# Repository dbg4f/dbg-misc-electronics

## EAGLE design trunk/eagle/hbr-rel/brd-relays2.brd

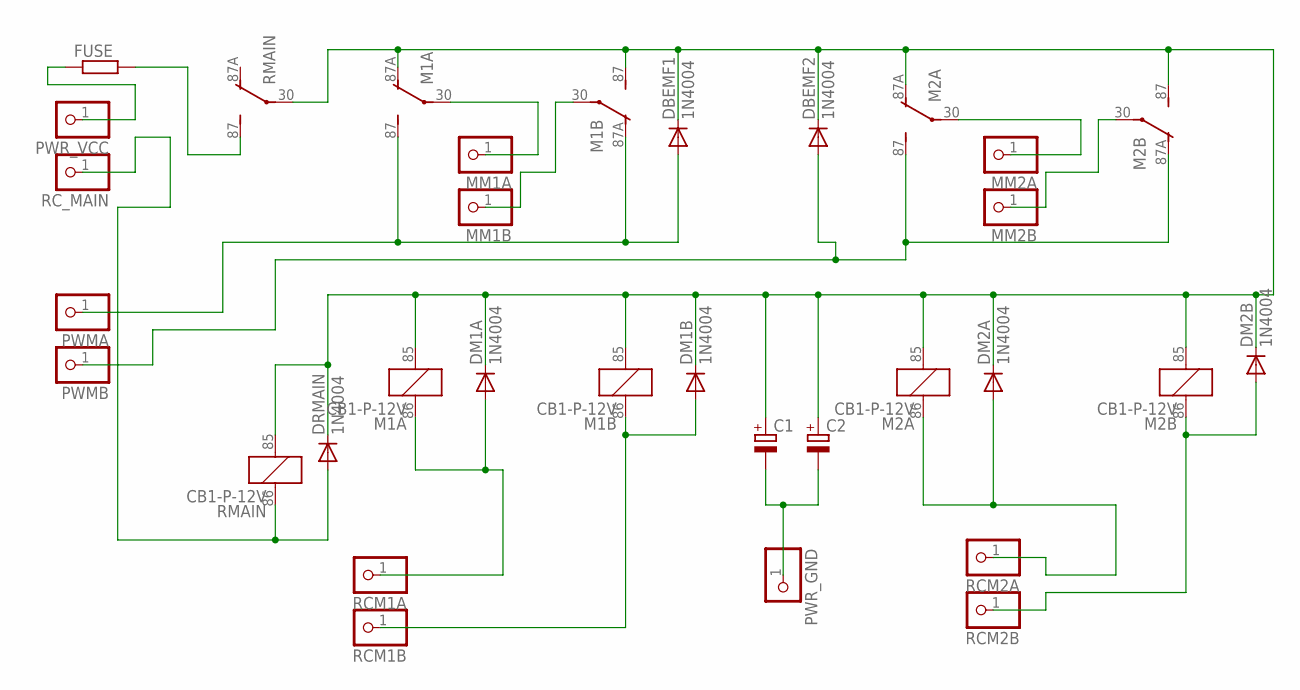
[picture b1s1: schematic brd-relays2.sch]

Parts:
C1, C2: CPOL-EUE5-13; E5-13
DBEMF1, DBEMF2: 1N4004; DO41-10
DM1A, DM1B, DM2A, DM2B: 1N4004; DO41-10
DRMAIN: 1N4004; DO41-10
FUSE: R-EU_0207/10; FUSE_PACK1
M1A, M1B, M2A, M2B: CB1-P-12V; CB1
MM1A, MM1B, MM2A, MM2B: PINHD-1X1; 1X01
PWMA: PINHD-1X1; 1X01
PWMB: PINHD-1X1; 1X01
PWR_GND: PINHD-1X1; 1X01
PWR_VCC: PINHD-1X1; 1X01
RCM1A, RCM1B, RCM2A, RCM2B: PINHD-1X1; 1X01
RC_MAIN: PINHD-1X1; 1X01
RMAIN: CB1-P-12V; CB1

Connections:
unnamed: C1.+, C2.+, DBEMF1.C, DBEMF2.C, DM1A.C, DM1B.C, DM2A.C, DM2B.C, DRMAIN.C, M1A.85 (2), M1A.87A (O), M1B.85 (2), M1B.87 (S), M2A.85 (2), M2A.87A (O), M2B.85 (2), M2B.87 (S), RMAIN.30, RMAIN.85 (2)
unnamed: M1A.30, MM1A.1
unnamed: M1B.30, MM1B.1
unnamed: FUSE.2, RMAIN.87 (S)
unnamed: DBEMF1.A, M1A.87 (S), M1B.87A (O), PWMA.1
unnamed: C1.-, C2.-, PWR_GND.1
unnamed: M2A.30, MM2A.1
unnamed: M2B.30, MM2B.1
unnamed: DM1A.A, M1A.86 (1), RCM1A.1
unnamed: DM1B.A, M1B.86 (1), RCM1B.1
unnamed: DM2A.A, M2A.86 (1), RCM2A.1
unnamed: DM2B.A, M2B.86 (1), RCM2B.1
unnamed: DBEMF2.A, M2A.87 (S), M2B.87A (O), PWMB.1
unnamed: DRMAIN.A, RC_MAIN.1, RMAIN.86 (1)
unnamed: FUSE.1, PWR_VCC.1

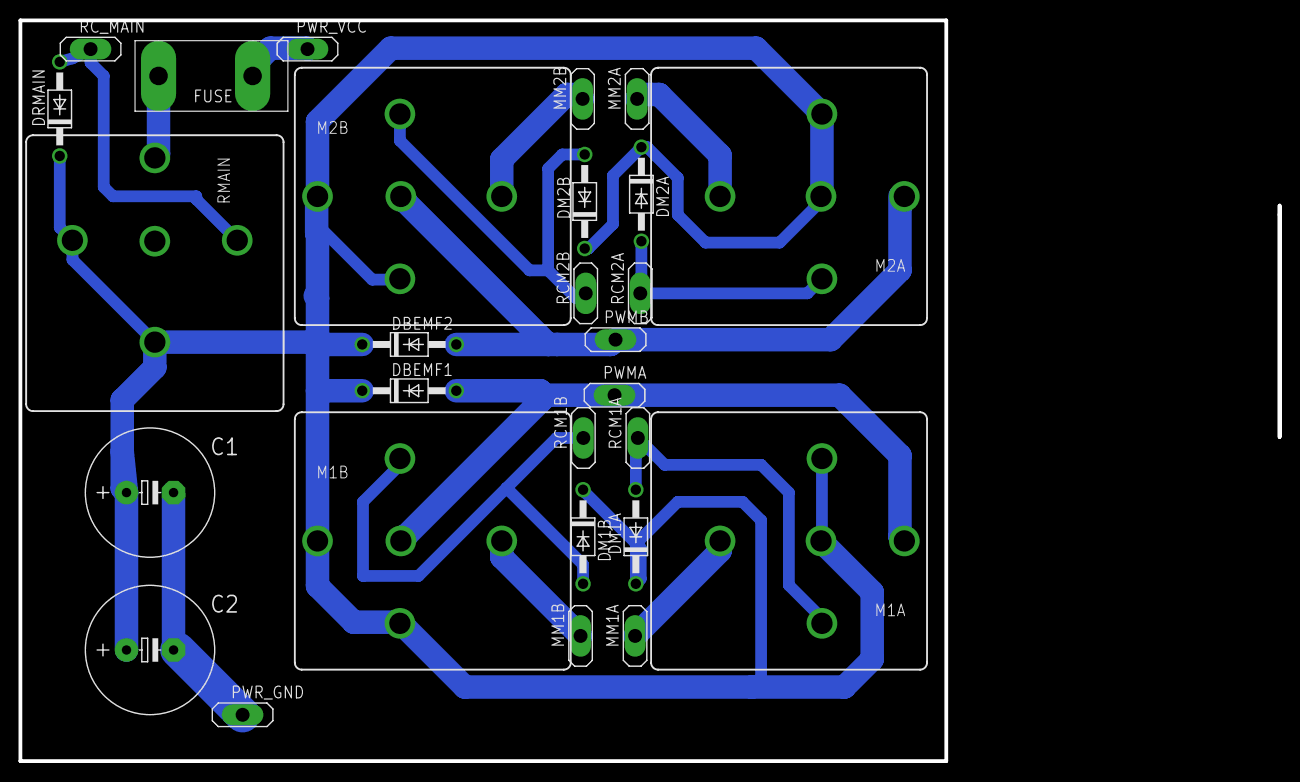
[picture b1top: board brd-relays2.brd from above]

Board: 2 copper layers, 100.0 x 80.0 mm, 28 parts (0 on the bottom side), 15 nets.

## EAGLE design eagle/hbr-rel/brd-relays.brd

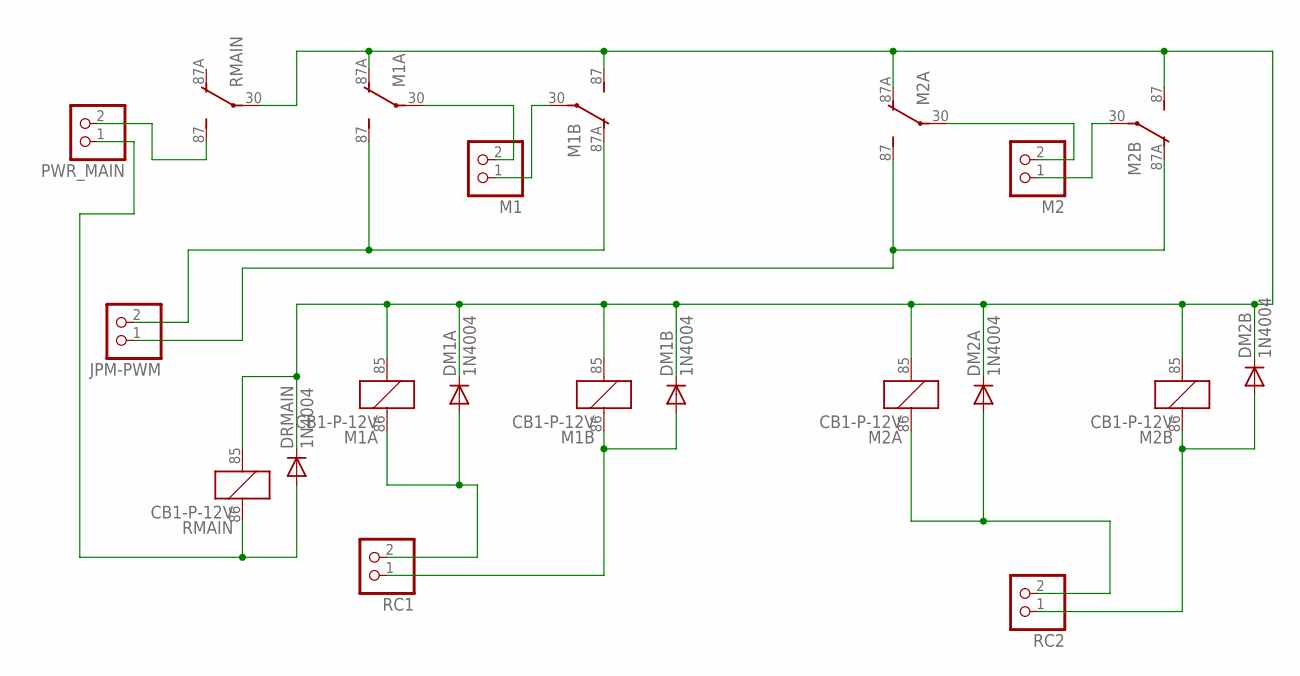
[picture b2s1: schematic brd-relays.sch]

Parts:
DM1A, DM1B, DM2A, DM2B: 1N4004; DO41-10
DRMAIN: 1N4004; DO41-10
JPM-PWM: PINHD-1X22X1-BIG; 1X02
M1, M2: PINHD-1X22X1-BIG; 1X02
M1A, M1B, M2A, M2B: CB1-P-12V; CB1
PWR_MAIN: PINHD-1X22X1-BIG; 1X02
RC1, RC2: PINHD-1X22X1-BIG; 1X02
RMAIN: CB1-P-12V; CB1

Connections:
unnamed: DM1A.C, DM1B.C, DM2A.C, DM2B.C, DRMAIN.C, M1A.85 (2), M1A.87A (O), M1B.85 (2), M1B.87 (S), M2A.85 (2), M2A.87A (O), M2B.85 (2), M2B.87 (S), RMAIN.30, RMAIN.85 (2)
unnamed: M1.2, M1A.30
unnamed: M1.1, M1B.30
unnamed: PWR_MAIN.2, RMAIN.87 (S)
unnamed: JPM-PWM.2, M1A.87 (S), M1B.87A (O)
unnamed: M2.2, M2A.30
unnamed: M2.1, M2B.30
unnamed: DM1A.A, M1A.86 (1), RC1.2
unnamed: DM1B.A, M1B.86 (1), RC1.1
unnamed: DM2A.A, M2A.86 (1), RC2.2
unnamed: DM2B.A, M2B.86 (1), RC2.1
unnamed: JPM-PWM.1, M2A.87 (S), M2B.87A (O)
unnamed: DRMAIN.A, PWR_MAIN.1, RMAIN.86 (1)

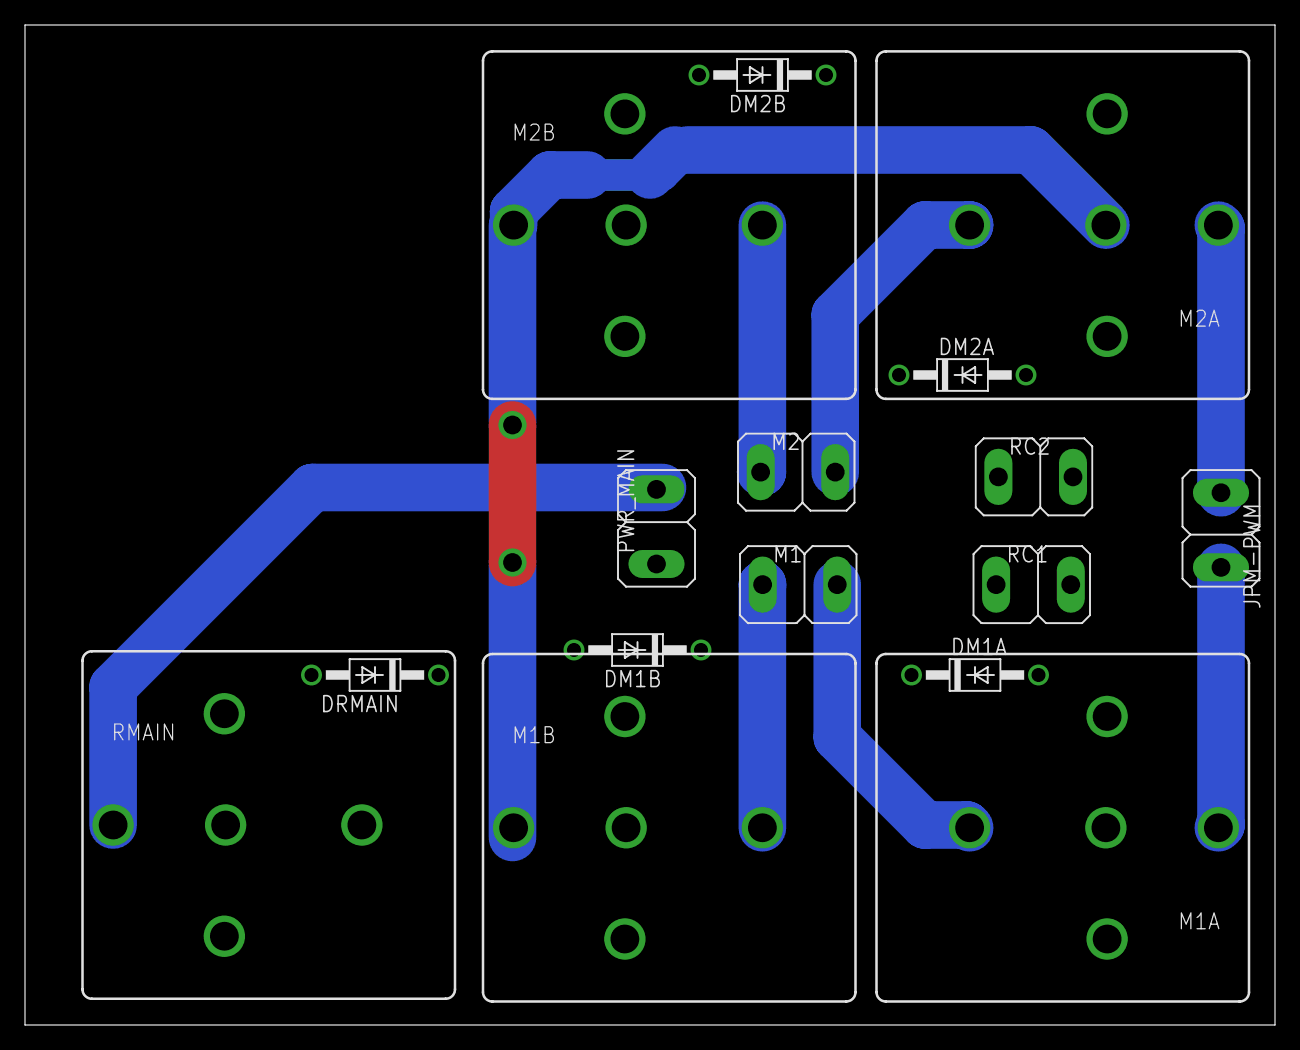
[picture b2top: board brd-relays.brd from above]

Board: 2 copper layers, 100.0 x 80.0 mm, 16 parts (0 on the bottom side), 13 nets.

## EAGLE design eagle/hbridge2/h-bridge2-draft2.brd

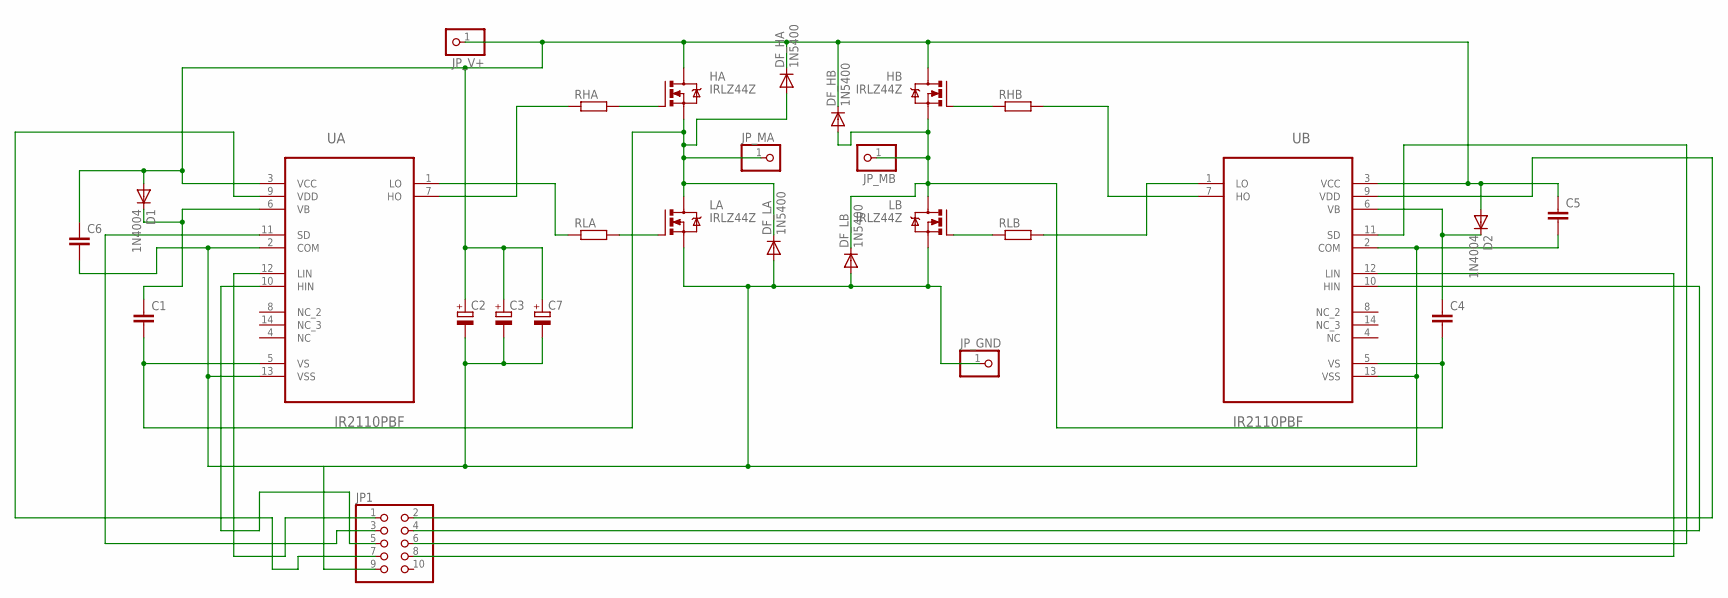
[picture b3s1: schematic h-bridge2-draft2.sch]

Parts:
C1, C4, C5, C6: C-EU025-025X050; C025-025X050
C2, C3, C7: CPOL-EUE5-13; E5-13
D1, D2: 1N4004; DO41-10
DF_HA: 1N5400; DO201-15
DF_HB: 1N5400; DO201-15
DF_LA: 1N5400; DO201-15
DF_LB: 1N5400; DO201-15
HA: IRLZ44Z; TO220BH
HB: IRLZ44Z; TO220BH
JP1: PINHD-2X5; 2X05
JP_GND: PINHD-1X1; 1X01
JP_MA: PINHD-1X1; 1X01
JP_MB: PINHD-1X1; 1X01
JP_V+: PINHD-1X1; 1X01
LA: IRLZ44Z; TO220BH
LB: IRLZ44Z; TO220BH
RHA: R-EU_0411/15; 0411/15
RHB: R-EU_0411/15; 0411/15
RLA: R-EU_0411/15; 0411/15
RLB: R-EU_0411/15; 0411/15
UA: IR2110PBF; DIP254P762X533-14
UB: IR2110PBF; DIP254P762X533-14

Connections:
unnamed: C2.-, C3.-, C5.2, C6.2, C7.-, DF_LA.A, DF_LB.A, JP1.9, JP_GND.1, LA.S, LB.S, UA.2 (COM), UA.13 (VSS), UB.2 (COM), UB.13 (VSS)
unnamed: LA.G, RLA.2
unnamed: HA.G, RHA.2
unnamed: HB.G, RHB.1
unnamed: LB.G, RLB.1
unnamed: RHA.1, UA.7 (HO)
unnamed: RLA.1, UA.1 (LO)
unnamed: RHB.2, UB.7 (HO)
unnamed: RLB.2, UB.1 (LO)
unnamed: C2.+, C3.+, C5.1, C6.1, C7.+, D1.A, D2.A, DF_HA.C, DF_HB.C, HA.D, HB.D, JP_V+.1, UA.3 (VCC), UB.3 (VCC)
unnamed: C1.1, D1.C, UA.6 (VB)
unnamed: C4.2, DF_HB.A, DF_LB.C, HB.S, JP_MB.1, LB.D, UB.5 (VS)
unnamed: C1.2, DF_HA.A, DF_LA.C, HA.S, JP_MA.1, LA.D, UA.5 (VS)
unnamed: C4.1, D2.C, UB.6 (VB)
unnamed: JP1.3, UA.11 (SD)
unnamed: JP1.7, UA.9 (VDD)
unnamed: JP1.5, UA.10 (HIN)
unnamed: JP1.1, UA.12 (LIN)
unnamed: JP1.2, UB.9 (VDD)
unnamed: JP1.4, UB.10 (HIN)
unnamed: JP1.6, UB.11 (SD)
unnamed: JP1.8, UB.12 (LIN)

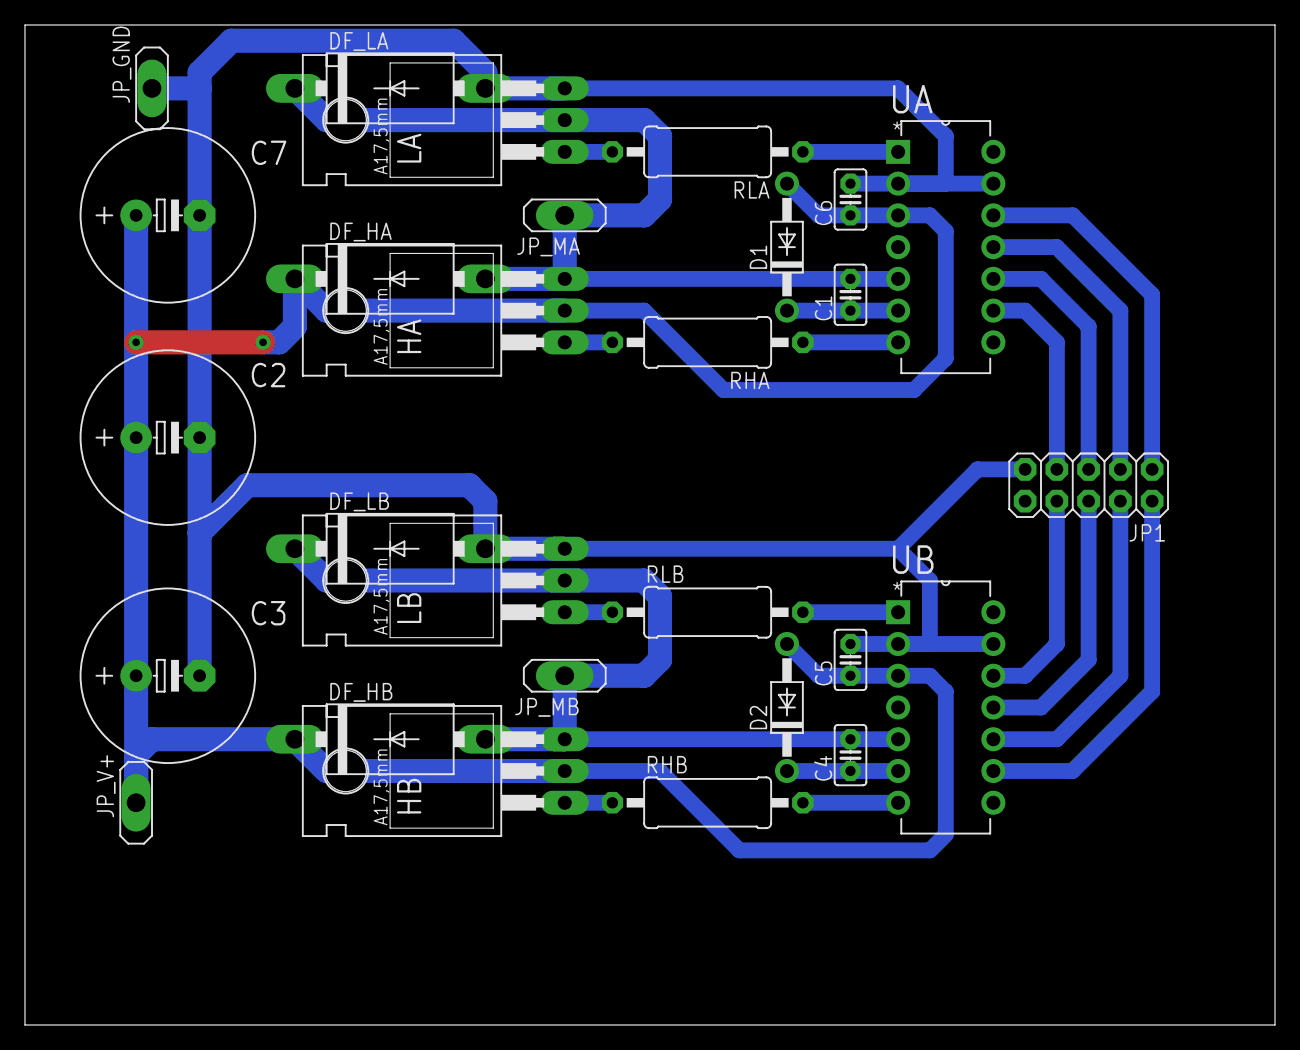
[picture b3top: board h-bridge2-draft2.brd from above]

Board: 2 copper layers, 100.0 x 80.0 mm, 28 parts (0 on the bottom side), 22 nets.

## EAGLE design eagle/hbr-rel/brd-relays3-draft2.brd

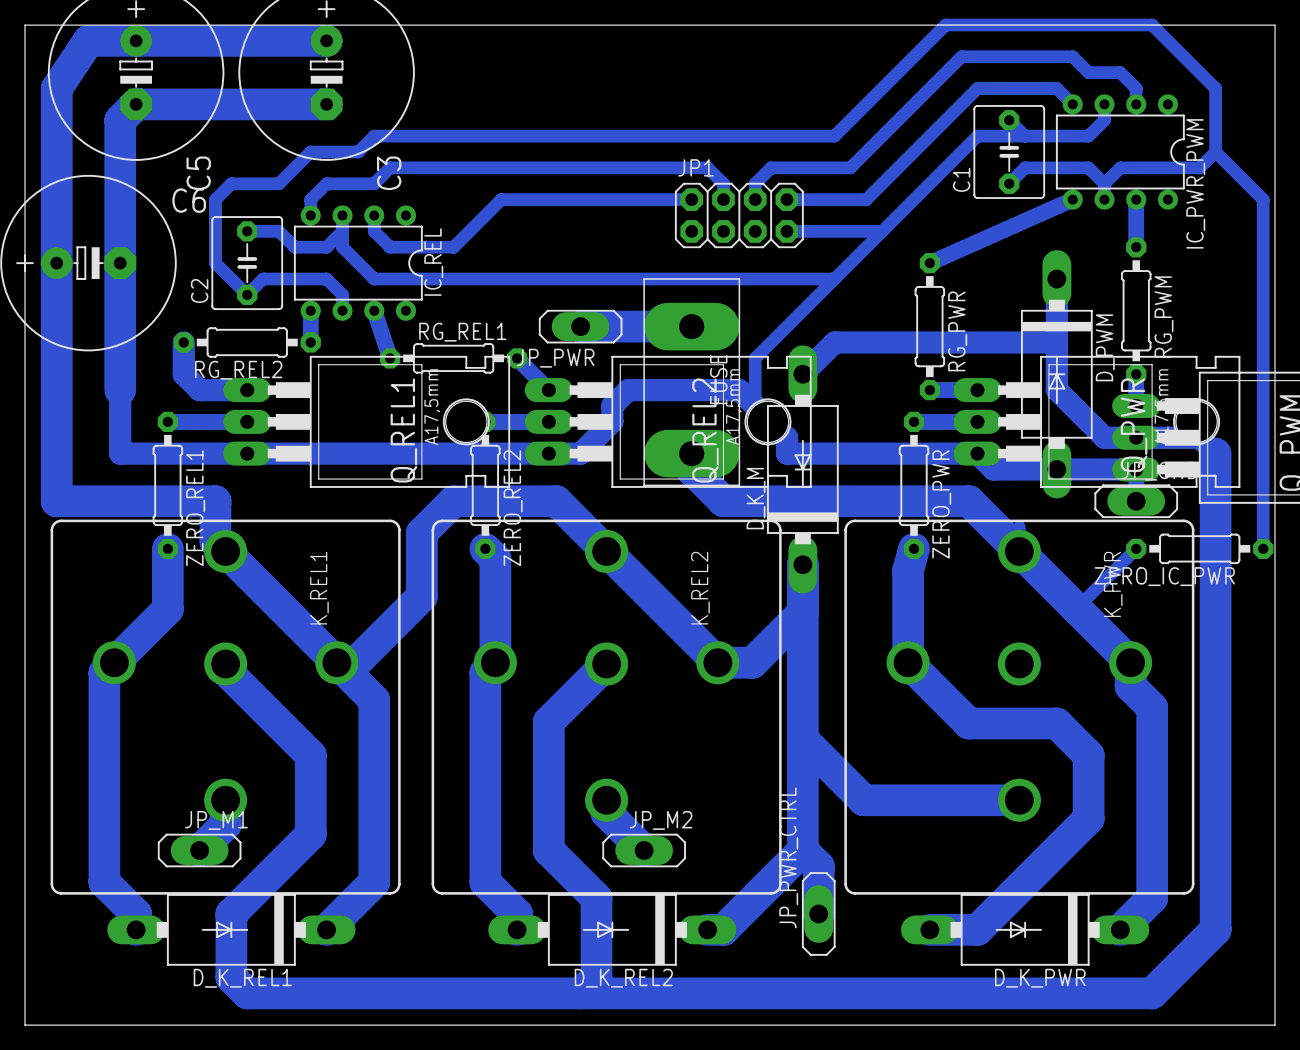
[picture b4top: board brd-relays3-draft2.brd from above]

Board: 2 copper layers, 100.0 x 80.0 mm, 34 parts (0 on the bottom side), 26 nets.

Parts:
C1, C2: C050-055X075
C3, C5, C6: E5-13
D_K_M: BY251; DO201-15
D_K_PWR: BY251; DO201-15
D_K_REL1, D_K_REL2: BY251; DO201-15
D_PWM: BY251; DO201-15
FUSE: FUSE_PACK1
IC_PWR_PWM: IR4427; DIL08
IC_REL: IR4427; DIL08
JP1: 2X04
JP_GND: 1X01
JP_M1, JP_M2: 1X01
JP_PWR: 1X01
JP_PWR_CTRL: 1X01
K_PWR: CB1-P-12V; CB1
K_REL1, K_REL2: CB1-P-12V; CB1
Q_PWM: IRLZ44Z; TO220BH
Q_PWR: IRLZ44Z; TO220BH
Q_REL1, Q_REL2: IRLZ44Z; TO220BH
RG_PWM: 0207/10
RG_PWR: 0207/10
RG_REL1, RG_REL2: 0207/10
ZERO_IC_PWR: 0207/10
ZERO_PWR: 0207/10
ZERO_REL1, ZERO_REL2: 0207/10

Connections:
GND: C1.2, C2.2, C3.-, C5.-, C6.-, D_PWM.A, IC_PWR_PWM.3, IC_REL.3, JP1.7, JP_GND.1, Q_PWM.S, Q_PWR.S, Q_REL1.S, Q_REL2.S
unnamed: FUSE.1, JP_PWR.1
unnamed: JP_M2.1, K_REL2.30
unnamed: IC_PWR_PWM.7, RG_PWM.1
unnamed: IC_PWR_PWM.5, RG_PWR.1
unnamed: Q_PWM.G, RG_PWM.2
unnamed: Q_PWR.G, RG_PWR.2
unnamed: IC_REL.7, RG_REL1.1
unnamed: Q_REL2.G, RG_REL1.2
unnamed: IC_REL.5, RG_REL2.1
unnamed: Q_REL1.G, RG_REL2.2
unnamed: IC_REL.2, JP1.2
unnamed: IC_REL.4, JP1.4
unnamed: IC_PWR_PWM.2, JP1.6
unnamed: D_K_PWR.C, FUSE.2, K_PWR.86, K_PWR.87, ZERO_IC_PWR.2
unnamed: D_K_PWR.A, K_PWR.85, ZERO_PWR.2
unnamed: IC_PWR_PWM.4, JP1.8
unnamed: JP_M1.1, K_REL1.30
unnamed: Q_REL1.D, ZERO_REL1.1
unnamed: Q_REL2.D, ZERO_REL2.1
unnamed: Q_PWR.D, ZERO_PWR.1
unnamed: D_K_M.A, D_PWM.C, K_REL1.87A, K_REL2.87A, Q_PWM.D
unnamed: D_K_REL1.A, K_REL1.85, ZERO_REL1.2
unnamed: C3.+, C5.+, C6.+, D_K_M.C, D_K_REL1.C, D_K_REL2.C, JP_PWR_CTRL.1, K_PWR.30, K_REL1.86, K_REL1.87, K_REL2.86, K_REL2.87
unnamed: D_K_REL2.A, K_REL2.85, ZERO_REL2.2
VCC: C1.1, C2.1, IC_PWR_PWM.6, IC_REL.6, ZERO_IC_PWR.1

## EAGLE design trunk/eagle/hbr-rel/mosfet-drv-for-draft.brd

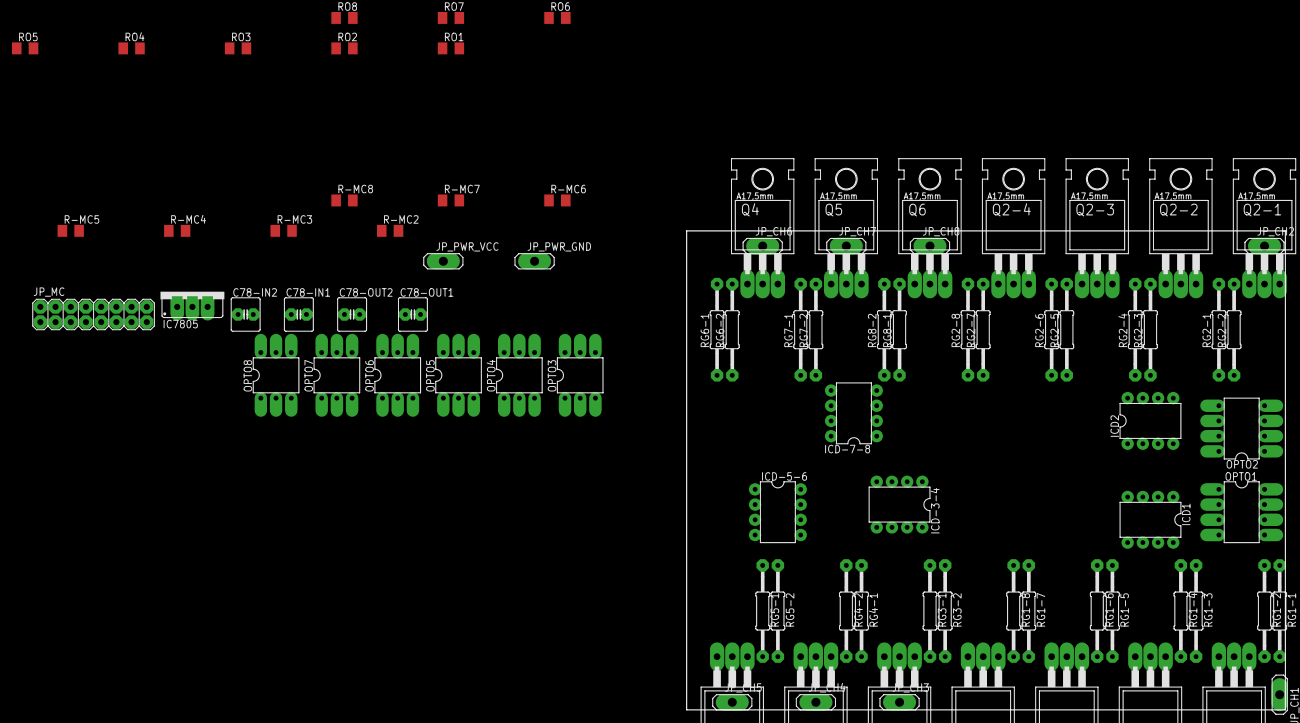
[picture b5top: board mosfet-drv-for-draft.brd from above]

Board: 2 copper layers, 100.0 x 80.0 mm, 87 parts (1 on the bottom side), 58 nets, no tracks yet.

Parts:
C78-IN1, C78-IN2, C78-OUT1, C78-OUT2: C025-060X050
IC7805: 78XXS
ICD1, ICD2: IR4427; DIL08
ICD-3-4, ICD-5-6, ICD-7-8: IR4427; DIL08
JP_CH1, JP_CH2, JP_CH3, JP_CH4, JP_CH5, JP_CH6, JP_CH7, JP_CH8: 1X01
JP_MC: 2X08
JP_PWR_GND: 1X01
JP_PWR_VCC: 1X01
OPTO1, OPTO2: 6N137; DIL08
OPTO3, OPTO4, OPTO5, OPTO6, OPTO7, OPTO8: 4N25M; DIL06
Q1, Q1-1, Q1-2, Q1-3, Q1-4, Q2, Q2-1, Q2-2, Q2-3, Q2-4, Q3, Q4, Q5, Q6: IRLZ44Z; TO220BH
R-MC1, R-MC2, R-MC3, R-MC4, R-MC5, R-MC6, R-MC7, R-MC8: M1206
RG1-1, RG1-2, RG1-3, RG1-4, RG1-5, RG1-6, RG1-7, RG1-8, RG2-1, RG2-2, RG2-3, RG2-4, RG2-5, RG2-6, RG2-7, RG2-8, RG3-1, RG3-2, RG4-1, RG4-2, RG5-1, RG5-2, RG6-1, RG6-2, RG7-1, RG7-2, RG8-1, RG8-2: 0207/15
RO1, RO2, RO3, RO4, RO5, RO6, RO7, RO8: M1206

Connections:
unnamed: C78-IN1.2, C78-IN2.2, C78-OUT1.2, C78-OUT2.2, IC7805.GND, ICD1.3, ICD2.3, ICD-3-4.3, ICD-5-6.3, ICD-7-8.3, JP_PWR_GND.1, OPTO1.5, OPTO2.5, OPTO3.4, OPTO4.4, OPTO5.4, OPTO6.4, OPTO7.4, OPTO8.4, Q1.S, Q1-1.S, Q1-2.S, Q1-3.S, Q1-4.S, Q2.S, Q2-1.S, Q2-2.S, Q2-3.S, Q2-4.S, Q3.S, Q4.S, Q5.S, Q6.S
unnamed: C78-IN1.1, C78-IN2.1, IC7805.IN, ICD1.6, ICD2.6, ICD-3-4.6, ICD-5-6.6, ICD-7-8.6, JP_PWR_VCC.1
unnamed: C78-OUT1.1, C78-OUT2.1, IC7805.OUT, OPTO1.8, OPTO2.8, RO1.2, RO2.2, RO3.2, RO4.2, RO5.2, RO6.2, RO7.2, RO8.2
unnamed: OPTO1.2, R-MC1.2
unnamed: OPTO2.2, R-MC2.2
unnamed: OPTO3.1, R-MC3.2
unnamed: OPTO4.1, R-MC4.2
unnamed: OPTO5.1, R-MC5.2
unnamed: OPTO6.1, R-MC6.2
unnamed: OPTO7.1, R-MC7.2
unnamed: OPTO8.1, R-MC8.2
unnamed: JP_MC.2, R-MC1.1
unnamed: JP_MC.4, R-MC2.1
unnamed: JP_MC.6, R-MC3.1
unnamed: JP_MC.8, R-MC4.1
unnamed: JP_MC.10, R-MC5.1
unnamed: JP_MC.12, R-MC6.1
unnamed: JP_MC.14, R-MC7.1
unnamed: JP_MC.16, R-MC8.1
unnamed: ICD1.2, ICD1.4, OPTO1.6, RO1.1
unnamed: JP_MC.15, OPTO1.3, OPTO2.3, OPTO3.2, OPTO4.2, OPTO5.2, OPTO6.2, OPTO7.2, OPTO8.2
unnamed: ICD2.2, ICD2.4, OPTO2.6, RO2.1
unnamed: ICD-3-4.2, OPTO3.6, RO3.1
unnamed: ICD-3-4.4, OPTO4.6, RO4.1
unnamed: ICD-5-6.2, OPTO5.6, RO5.1
unnamed: ICD-5-6.4, OPTO6.6, RO6.1
unnamed: ICD-7-8.2, OPTO7.6, RO7.1
unnamed: ICD-7-8.4, OPTO8.6, RO8.1
unnamed: Q1-1.G, RG1-1.2, RG1-2.2
unnamed: ICD1.5, ICD1.7, RG1-1.1, RG1-2.1, RG1-3.1, RG1-4.1, RG1-5.1, RG1-6.1, RG1-7.1, RG1-8.1
unnamed: Q1-2.G, RG1-3.2, RG1-4.2
unnamed: Q1-3.G, RG1-5.2, RG1-6.2
unnamed: Q1-4.G, RG1-7.2, RG1-8.2
unnamed: Q2-1.G, RG2-1.2, RG2-2.2
unnamed: JP_CH1.1, Q1-1.D, Q1-2.D, Q1-3.D, Q1-4.D
unnamed: ICD2.5, ICD2.7, RG2-1.1, RG2-2.1, RG2-3.1, RG2-4.1, RG2-5.1, RG2-6.1, RG2-7.1, RG2-8.1
unnamed: Q2-2.G, RG2-3.2, RG2-4.2
unnamed: Q2-3.G, RG2-5.2, RG2-6.2
unnamed: Q2-4.G, RG2-7.2, RG2-8.2
unnamed: JP_CH2.1, Q2-1.D, Q2-2.D, Q2-3.D, Q2-4.D
unnamed: JP_CH3.1, Q3.D
unnamed: ICD-3-4.7, RG3-1.1, RG3-2.1
unnamed: Q3.G, RG3-1.2, RG3-2.2
unnamed: ICD-3-4.5, RG4-1.1, RG4-2.1
unnamed: Q1.G, RG4-1.2, RG4-2.2
unnamed: JP_CH4.1, Q1.D
unnamed: ICD-7-8.5, RG8-1.1, RG8-2.1
unnamed: ICD-5-6.7, RG5-1.1, RG5-2.1
unnamed: Q2.G, RG5-1.2, RG5-2.2
unnamed: JP_CH5.1, Q2.D
unnamed: ICD-7-8.7, RG7-1.1, RG7-2.1
unnamed: ICD-5-6.5, RG6-1.1, RG6-2.1
unnamed: Q4.G, RG6-1.2, RG6-2.2
unnamed: JP_CH6.1, Q4.D
unnamed: Q6.G, RG8-1.2, RG8-2.2
unnamed: JP_CH8.1, Q6.D
unnamed: Q5.G, RG7-1.2, RG7-2.2
unnamed: JP_CH7.1, Q5.D

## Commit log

2011-04-27 Initial directory structure.
2011-04-27 inital copy to GCR
2011-05-13 INT0 handling added
2011-05-15 added hidmc
2011-05-16 Testing INT0
2011-05-28 Spring config added
2011-05-28 AVR: AIN used for
2011-05-30 AVR: different pin stickers
2011-10-09 added 2104 and others
2011-11-20 simple rate display swing widget
2011-11-20 HID Js input handling
2011-12-05 HID + mc using crc8
2011-12-09 AVR: custom registers access
2011-12-13 mc communication wrappers
2012-01-02 mc communication failover
2012-01-04 steering buffering
2012-01-10 steering buffering improvements, ivy.xml added, log4j
2012-01-10 living room added
2012-01-14 living room added, dynamic check-list implemented
2012-10-20 j3d libs descr
2012-10-22 mouse pwm driver
2012-11-26 motor pins swapped
2012-12-05 added m16 skeleton
2012-12-05 added m16 bootloader
2012-12-10 avrdude scripts for bootloader
2012-12-13 bootloader and test app for m16
2012-12-14 m16 regs
2012-12-15 ADC0 reading
2012-12-15 ADC0 communication
2012-12-15 m16 ADC reading support
2012-12-19 dashboard draft added
2013-01-12 robo drv draft setup with HID js input, screen and loggers
2013-01-14 robo drv draft setup with HID js input, screen and loggers, display HID device types and codes
2013-01-17 dashboard widgets extracted into separate classes, drive interfaced created
2013-01-25 restruturing directories
2013-01-25 restructuring
2013-01-25 spring ioc and log4j
2013-01-27 GenericThread, EventListener template
2013-01-28 Master Parameters definition, Head Controller
2013-01-30 Ranges enhancement and UT
2013-01-31 Stick Driver, Master Param Accessor
2013-02-01 Accessors, widgets to spring config
2013-02-02 Stick events flow connection with screen via head controller
2013-02-07 constants extracted to defines, Watchdog commands
2013-02-09 m16: ADC buffering, context
2013-02-11 adc tx buffering using ints
2013-02-19 signature
2013-02-28 counter context added
2013-03-10 response asynch mode
2013-03-12 avrdude net avr109 mode
2013-03-15 test commit
2013-03-15 command line widget prototype
2013-03-16 command line, cursor blinking
2013-03-16 mcu commands wrapper
2013-03-18 mcu communication construction
2013-03-19 self-synchronizing communication skeleton
2013-03-20 self-synchronizing communication
2013-03-22 command length fixed
2013-03-24 mcu report decoding bugs fixed
2013-03-26 mcu synchronous executor, simple time chart
2013-03-27 communications debug
2013-03-28 status listeners unified, consolidated drive state added
2013-03-30 drive statistics support
2013-03-31 integer value with history
2013-04-01 value with history chart
2013-04-03 spring config splitted, Stick connected to TimeSeriesChart
2013-04-03 charts snapshot to csv
2013-04-04 Multiple values with history in one chart
2013-09-03 port bits set/clear commands
2013-09-03 port set/clear bit command
2013-09-12 PWM impementaion on timer 1 (A,B), bit utils
2013-09-16 groovy console
2013-09-17 ver +1
2013-09-19 ADC logs to csv
2013-10-01 Timers setup for PWM mode
2013-10-02 command line evaluation
2013-10-03 groovy DSL-like sample
2013-10-03 command line evaluation with groovy
2013-10-04 command line features
2013-10-05 command line features, history recall by kbd arrows
2013-10-09 comments fixes
2013-10-10 components wiring by spring config
2013-10-11 M16 emulator based on mcu C code
2013-10-18 emulator ADC feed
2013-10-19 stat counters, emulator improvements
2013-10-19 emulator adc to chart
2013-10-19 communication controller insertion
2013-10-26 emulator and communication improvements
2013-11-07 drive testing on mcu and emulator
2013-11-17 debugging on a device
2013-11-20 ValueWithHistory enhancements, save, restore
2013-12-04 Atmega32u4 (leonardo) LUFA sample based
2013-12-07 Atmega32u4 (leonardo) LUFA sample based, reg access added
2013-12-08 Atmega32u4 (leonardo) LUFA sample based, ADC asynch transfer
2013-12-10 Atmega32u4 (leonardo) cleanup, INT0 counter
2013-12-18 Atmega32u4, PWM test
2013-12-25 Atmega32u4, Drv test
2013-12-25 Atmega32u4, Servo test, ADC sending on update only
2013-12-29 PID draft
2013-12-30 Servo Emulator
2013-12-31 Servo Emulator with PID and UI
2014-01-01 Steering with PID
2014-01-01 Steering with PID, ClockableController introduced
2014-01-04 Steering with PID, I and D tuning
2014-01-14 LUFA integration
2014-01-14 LUFA integration, restructuring
2014-01-14 Steering testing
2014-01-16 Moving PID and DRV to MCU
2014-01-18 Traction driver
2014-01-26 Initiated moving PID to MC
2014-02-03 Initiated moving PID to MC, L1 command set extended with Drv and PID
2014-06-15 eagle circuit and pcb
2014-06-29 h-bridge relays circuit and PCB, hw tested ok
2014-11-22 Cnc Calc for calibration
2015-03-31 Migrating wiki contents from Google Code
